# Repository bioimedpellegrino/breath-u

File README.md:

# Low-Cost Vital Monitoring Device for Infants

## Overview
This experimental thesis focuses on the design, implementation, and testing of a low-cost device intended for monitoring the vital functions of the wearer. The idea behind this device was conceived to offer parents greater control over their infants during the first year of life, with the aim of preventing unexpected deaths such as:

- Accidental suffocation,
- Positional asphyxia,
- Choking due to inhalation or regurgitation,
- And unexplained incidents like Sudden Infant Death Syndrome (SIDS).

In these cases, immediate detection of danger is critical to saving the infant's life and avoiding permanent brain damage.

Although the percentage of such deaths is fortunately very low, it is essential that parents have access to an affordable and highly reliable embedded system.

## Scope of the Thesis
This thesis will analyze the various stages involved in the development of the device, including:

- Conceptualization and design,
- Selection and application of sensors,
- Preliminary testing,
- Final experimentation.

The entire process is described from an engineering perspective, ensuring a comprehensive understanding of the project's development.

## Objectives
The primary objective of this work is to create a cost-effective and dependable system that allows real-time monitoring of an infant’s vital signs, contributing to the reduction of preventable infant deaths. The approach combines careful sensor selection and system design to ensure both practicality and efficiency.

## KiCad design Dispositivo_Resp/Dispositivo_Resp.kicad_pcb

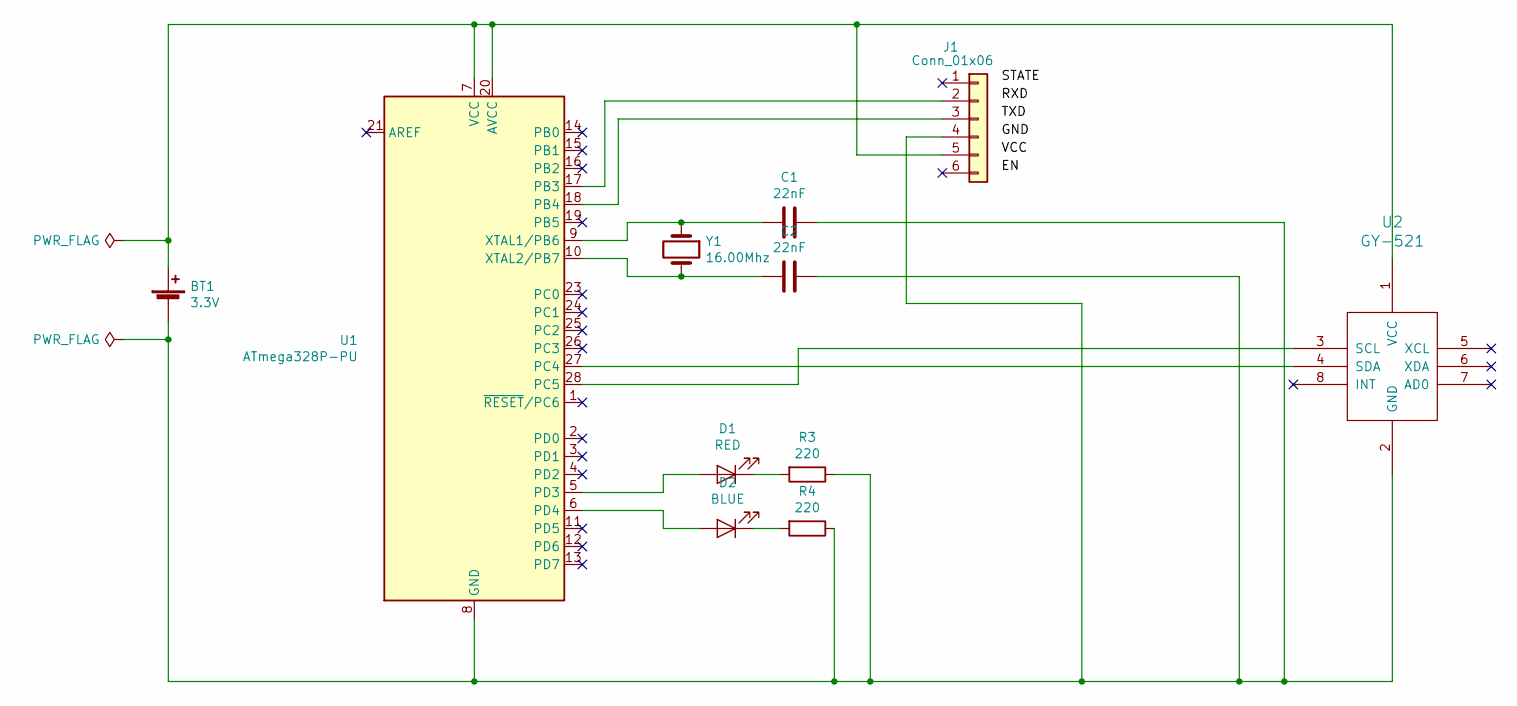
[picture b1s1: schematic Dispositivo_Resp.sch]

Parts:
BT1: 3.3V; PinSocket_1x02_P2.54mm_Horizontal
C1, C2: 22nF; C_Disc_D3.4mm_W2.1mm_P2.50mm
D1: RED; LED_D3.0mm
D2: BLUE; LED_D3.0mm
J1: Conn_01x06; PinSocket_1x06_P2.54mm_Horizontal
R3, R4: 220; R_Axial_DIN0207_L6.3mm_D2.5mm_P7.62mm_Horizontal
U1: ATmega328P-PU; DIL28
U2: GY-521; PinSocket_1x08_P2.54mm_Horizontal
Y1: 16.00Mhz; Crystal_HC18-U_Vertical

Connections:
unnamed: BT1.1 (+), J1.5, U1.7 (VCC), U1.20 (AVCC), U2.1 (VCC)
unnamed: BT1.2 (-), C1.1, C2.1, J1.4, R3.1, R4.1, U1.8 (GND), U1.22 (GND), U2.2 (GND)
unnamed: C1.2, U1.9 (XTAL1/PB6), Y1.1
unnamed: C2.2, U1.10 (XTAL2/PB7), Y1.2
unnamed: D1.1 (K), R3.2
unnamed: D1.2 (A), U1.5 (PD3)
unnamed: D2.1 (K), R4.2
unnamed: D2.2 (A), U1.6 (PD4)
unnamed: J1.2, U1.17 (PB3)
unnamed: J1.3, U1.18 (PB4)
unnamed: U1.27 (PC4), U2.4 (SDA)
unnamed: U1.28 (PC5), U2.3 (SCL)

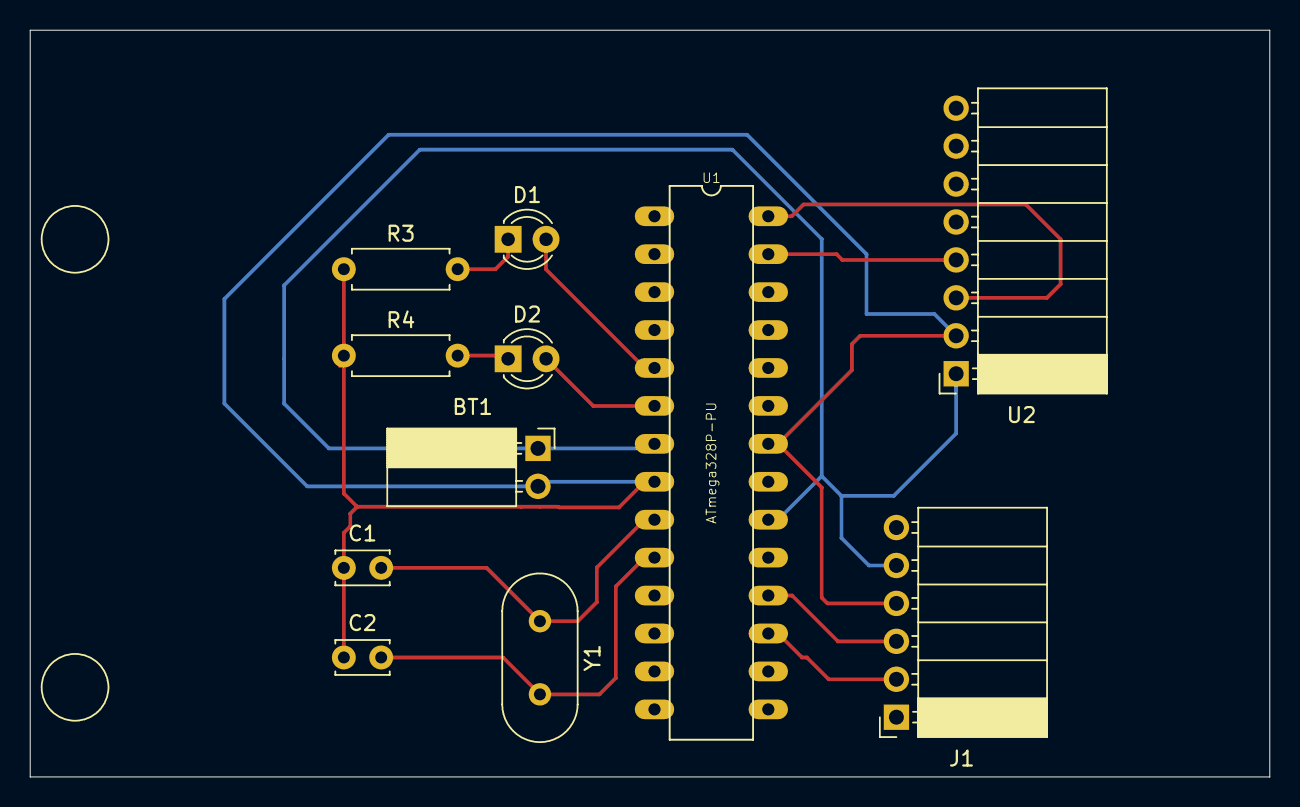
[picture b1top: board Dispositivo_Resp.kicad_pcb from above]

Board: 2 copper layers, 83.0 x 50.0 mm, 11 parts (0 on the bottom side), 12 nets.

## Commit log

2024-08-21 init repo
2024-08-21 remove useless folder
2024-08-21 add readme file
